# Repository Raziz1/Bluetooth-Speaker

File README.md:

# Bluetooth-Speaker 🛜🔊
 PCB design for a custom bluetooth speaker

<p align="center"><i>KiCad Render</i></p>

## Design Considerations
The goal of this project was to design a simple Bluetooth speaker using parts I already had at home, along with components available in the current KiCad library. This approach aimed to simplify the design process.
Based on the above goal I selected the following components: 

# Components

## ESP32 🖥️
* [ESP32-C3-WROOM-02](https://www.espressif.com/en/module/esp32-c3-wroom-02-en)
* I settled on this ESP32 module because it included the following essential features for this project:
    * Bluetooth 5
    * On-board PCB antenna
    * I2S (Inter-Integrated Circuit Sound)
    * Built-in USB Serial/JTAG Controller
* During my initial research, I planned to use the GPIO DACs to output the audio signal. However, I soon discovered that other models only offered 8-bit DACs, which were insufficient for modern audio quality. As a result, I decided to settle on a chip that supported I2S.
* Lastly, many ESP32 models require a USB to UART chip for programming. I chose this particular model because it has this functionality built in, allowing it to be directly wired to the USB port.

## Lithium Ion Battery 🔋
For the battery, I ended up selecting a pair of lithium-ion batteries I already had at home. The batteries were two 3.7V 2600mAh lithium-ion batteries from PKCELL. The batteries were initially going to be arranged in series in a battery pack to produce an output voltage of 7.4V and a capacity of 2600 mAh. However, after further research, I determined that using a single cell outputting 3.7V would significantly simplify the design. [Li-ion Battery ICR18650 2600mAh 3.7V Datasheet](https://www.parts-express.com/pedocs/specs/142-202--pkcell-flat-top-18650-li-ion-3.7v-2600mah-rechargeable-battery-spec-sheet.pdf). Some important specifications to note about this battery are the following:
* Nominal Voltage - 3.7V
* Charging Cut-off Voltage - 4.2V
* Discharge Cut-off Voltage - 3.0V
* Standard Charge - Constant Current 0.5C Constant Voltage 4.2V 0.01 C cut-off
* Standard Discharge - Discharge at 0.2 C to 3.0V

<p align="center"><i>PKCELL Lithium Ion Batteries</i></p>

## Audio Amplifier 
The audio amplifier was a key factor in determining my lithium-ion battery cell configuration. When selecting an amplifier, I had several requirements:
* It needed to output 2-5 watts with a 4-ohm speaker.
* It had to have built-in support for I2S to simplify the external circuitry.
* It required a low enough supply voltage to be compatible with either a 1S or 2S lithium-ion battery configuration.
Given these requirements, I opted for a Class D amplifier. These amplifiers are the most efficient, requiring the lowest supply voltage, which made them ideal for my battery-powered application.

### Power Considerations
* For Class D audio amplifiers under 5 watts, you can power them with a single 18650 3.7V cell, as they typically operate within a voltage range of 2.5 to 5.5V.
* For Class D audio amplifiers exceeding 5 watts, a higher supply voltage range is necessary, which typically requires a larger series battery configuration. However, when your battery configuration's supply voltage surpasses 5V, standard USB-C charging becomes insufficient. In this case, you have two options:
    1. Use a power delivery IC to negotiate higher voltages (9V, 12V, or 20V) from the wall socket.
    2. Implement a boost converter between the USB-C receptacle and the charger management IC.

I ended up settling on the [MAX98357A](https://www.analog.com/media/en/technical-documentation/data-sheets/MAX98357A-MAX98357B.pdf). Some important specifications to note about this battery are the following:
* Single-Supply Operation (2.5V to 5.5V)
* 3.2W Output Power into 4Ω at 5V
* Supports I2S data

## Charger Management IC
For the charger management IC I ended up settling on the [MAX1811](https://www.analog.com/media/en/technical-documentation/data-sheets/MAX1811.pdf) because of its simplicity and due to the fact it was already in the KiCad library.

# Firmware

# Schematic Design
## USB-C
For the USB-C interface, I opted for a minimal power delivery interface and simply added 5.1k pull-down resistors on both CC lines. Consequently, with a compatible power source (host), this device should be able to draw up to 3A of current.

## MAX1811 (Charging Management IC)
* Battery Regulation Voltage-Select Input was set to high so that the battery regulation set point is 4.20V
* Battery Regulation Current-Selection Input was set to high to default to a 500mA maximum battery regulation current.
    * This charger IC is on the slower side. There exists much higher power charger management IC'selected

## RT6150B-33GQW (Current Mode Buck-Boost Converter)
* The RT6150A/B is a high efficiency, fixed frequency, BuckBoost DC-DC converter that operates from input voltages above, below or equal to the output voltage.

### Inductor Selection
* ${L_1=\frac{V_{out}\cdot \left(V_{in\left(max\right)}-V_{out}\right)}{f\cdot ΔI_L\cdot V_{out}}=\frac{3.3\cdot \:\left(5-3.3\right)}{1E6\cdot 0.15\cdot \:3.3} = 7.48uH}$
* ${L_2=\frac{V_{in\left(min\right)}\cdot \:\left(V_{out}-V_{in\left(min\right)}\right)}{f\cdot \:ΔI_L\cdot \:V_{out}}=\frac{3.1\cdot \:\:\left(3.3-3.1\right)}{1E6\cdot \:0.150\cdot \:\:3.3}=1.25uH}$
* ${ΔI_L}$ The ripple current was chosen to be 30% of the suggested ESP32 power supply output current of at least 500mA.
* The datasheet suggests <i>"The recommended inductor value range is between 1.5μH and 4.7μH."</i>
* Therefore, based on the datasheets suggestions and calculations a reasonable middle ground was to select an inductance of 4.7uH.

### Output Capacitor Selection
* ${ΔV_{out},\:peak\:\left(Buck\right)=100mV=\frac{V_{out}\cdot \:\left(V_{in}-V_{out}\right)}{V_{in}\cdot \:8\cdot \:L\cdot \:\left(f_{osc}\right)^2\cdot \:C_{out}}=\frac{3.3\cdot \:\left(5-3.3\right)}{5\cdot \:8\cdot \:\left(4.7E-6\right)\cdot \:\left(1E6\right)^2\cdot \:C_{out}}\rightarrow C_{out}=2.98E-7F}$
* ${ΔV_{out},\:peak\:\left(Boost\right)=100mV=\frac{I_{Load}\cdot \left(V_{out}-V_{in}\right)}{C_{out}\cdot V_{out}\cdot f_{osc}}=\frac{0.5\:\cdot \:\left(3.3-3.1\right)}{C_{out}\cdot \:3.3\cdot \:\left(1E6\right)}\rightarrow C_{out}=3.03E-7F}$
* The above calculations assume an output ripple voltage of 100mV. Given that said we will use the value that is used on the Raspberry Pi PICO (47uF) which is significantly higher and will result in a significantly smaller output ripple voltage.

### Thermal Considerations
* PD(MAX) = (125°C − 25°C) / (30.5°C/W) = 3.28W for
WDFN-10L 3x3 package

* PD(MAX) = (125°C − 25°C) / (40.9°C/W) = 2.44W for
WDFN-10L 2.5x2.5 package 

# PCB Layout

# BOM

# Characterization

# Resources
* [How to design an ESP32 PCB with KiCad (in less than 25 minutes)
](https://www.youtube.com/watch?v=jiJGbWOSdMo)
* [ESP32 + PCB Antenna Hardware Design Tutorial - Phil's Lab #90
](https://www.youtube.com/watch?v=yxU_Kw2de08)
* [ESP32 PCB Layout Design](https://docs.espressif.com/projects/esp-hardware-design-guidelines/en/latest/esp32c2/pcb-layout-design.html)
* [All About USB-C: Example Circuits
](https://hackaday.com/2023/08/07/all-about-usb-c-example-circuits/)
* [ESP32 Dev Kit Schematic Example](https://dl.espressif.com/dl/schematics/SCH_ESP32-C3-DEVKITC-02_V1_1_20210126A.pdf)
* [I2S MAX98357 Bluetooth Speaker project for ESP32 microcontroller / Programming Arduino IDE](https://www.youtube.com/watch?v=24pk28oqVQI)
* [ESP32 Audio Output with I2S DMA and the MAX98357A Class D Amplifier](https://www.youtube.com/watch?v=At8PDQ3g7FQ)
* [ESP32-A2DP](https://github.com/pschatzmann/ESP32-A2DP)
* [ESP32 DAC Audio Analog Output With Examples (Arduino IDE)](https://deepbluembedded.com/esp32-dac-audio-arduino-examples/)
* [Sound with ESP32 – I2S Protocol](https://dronebotworkshop.com/esp32-i2s/)

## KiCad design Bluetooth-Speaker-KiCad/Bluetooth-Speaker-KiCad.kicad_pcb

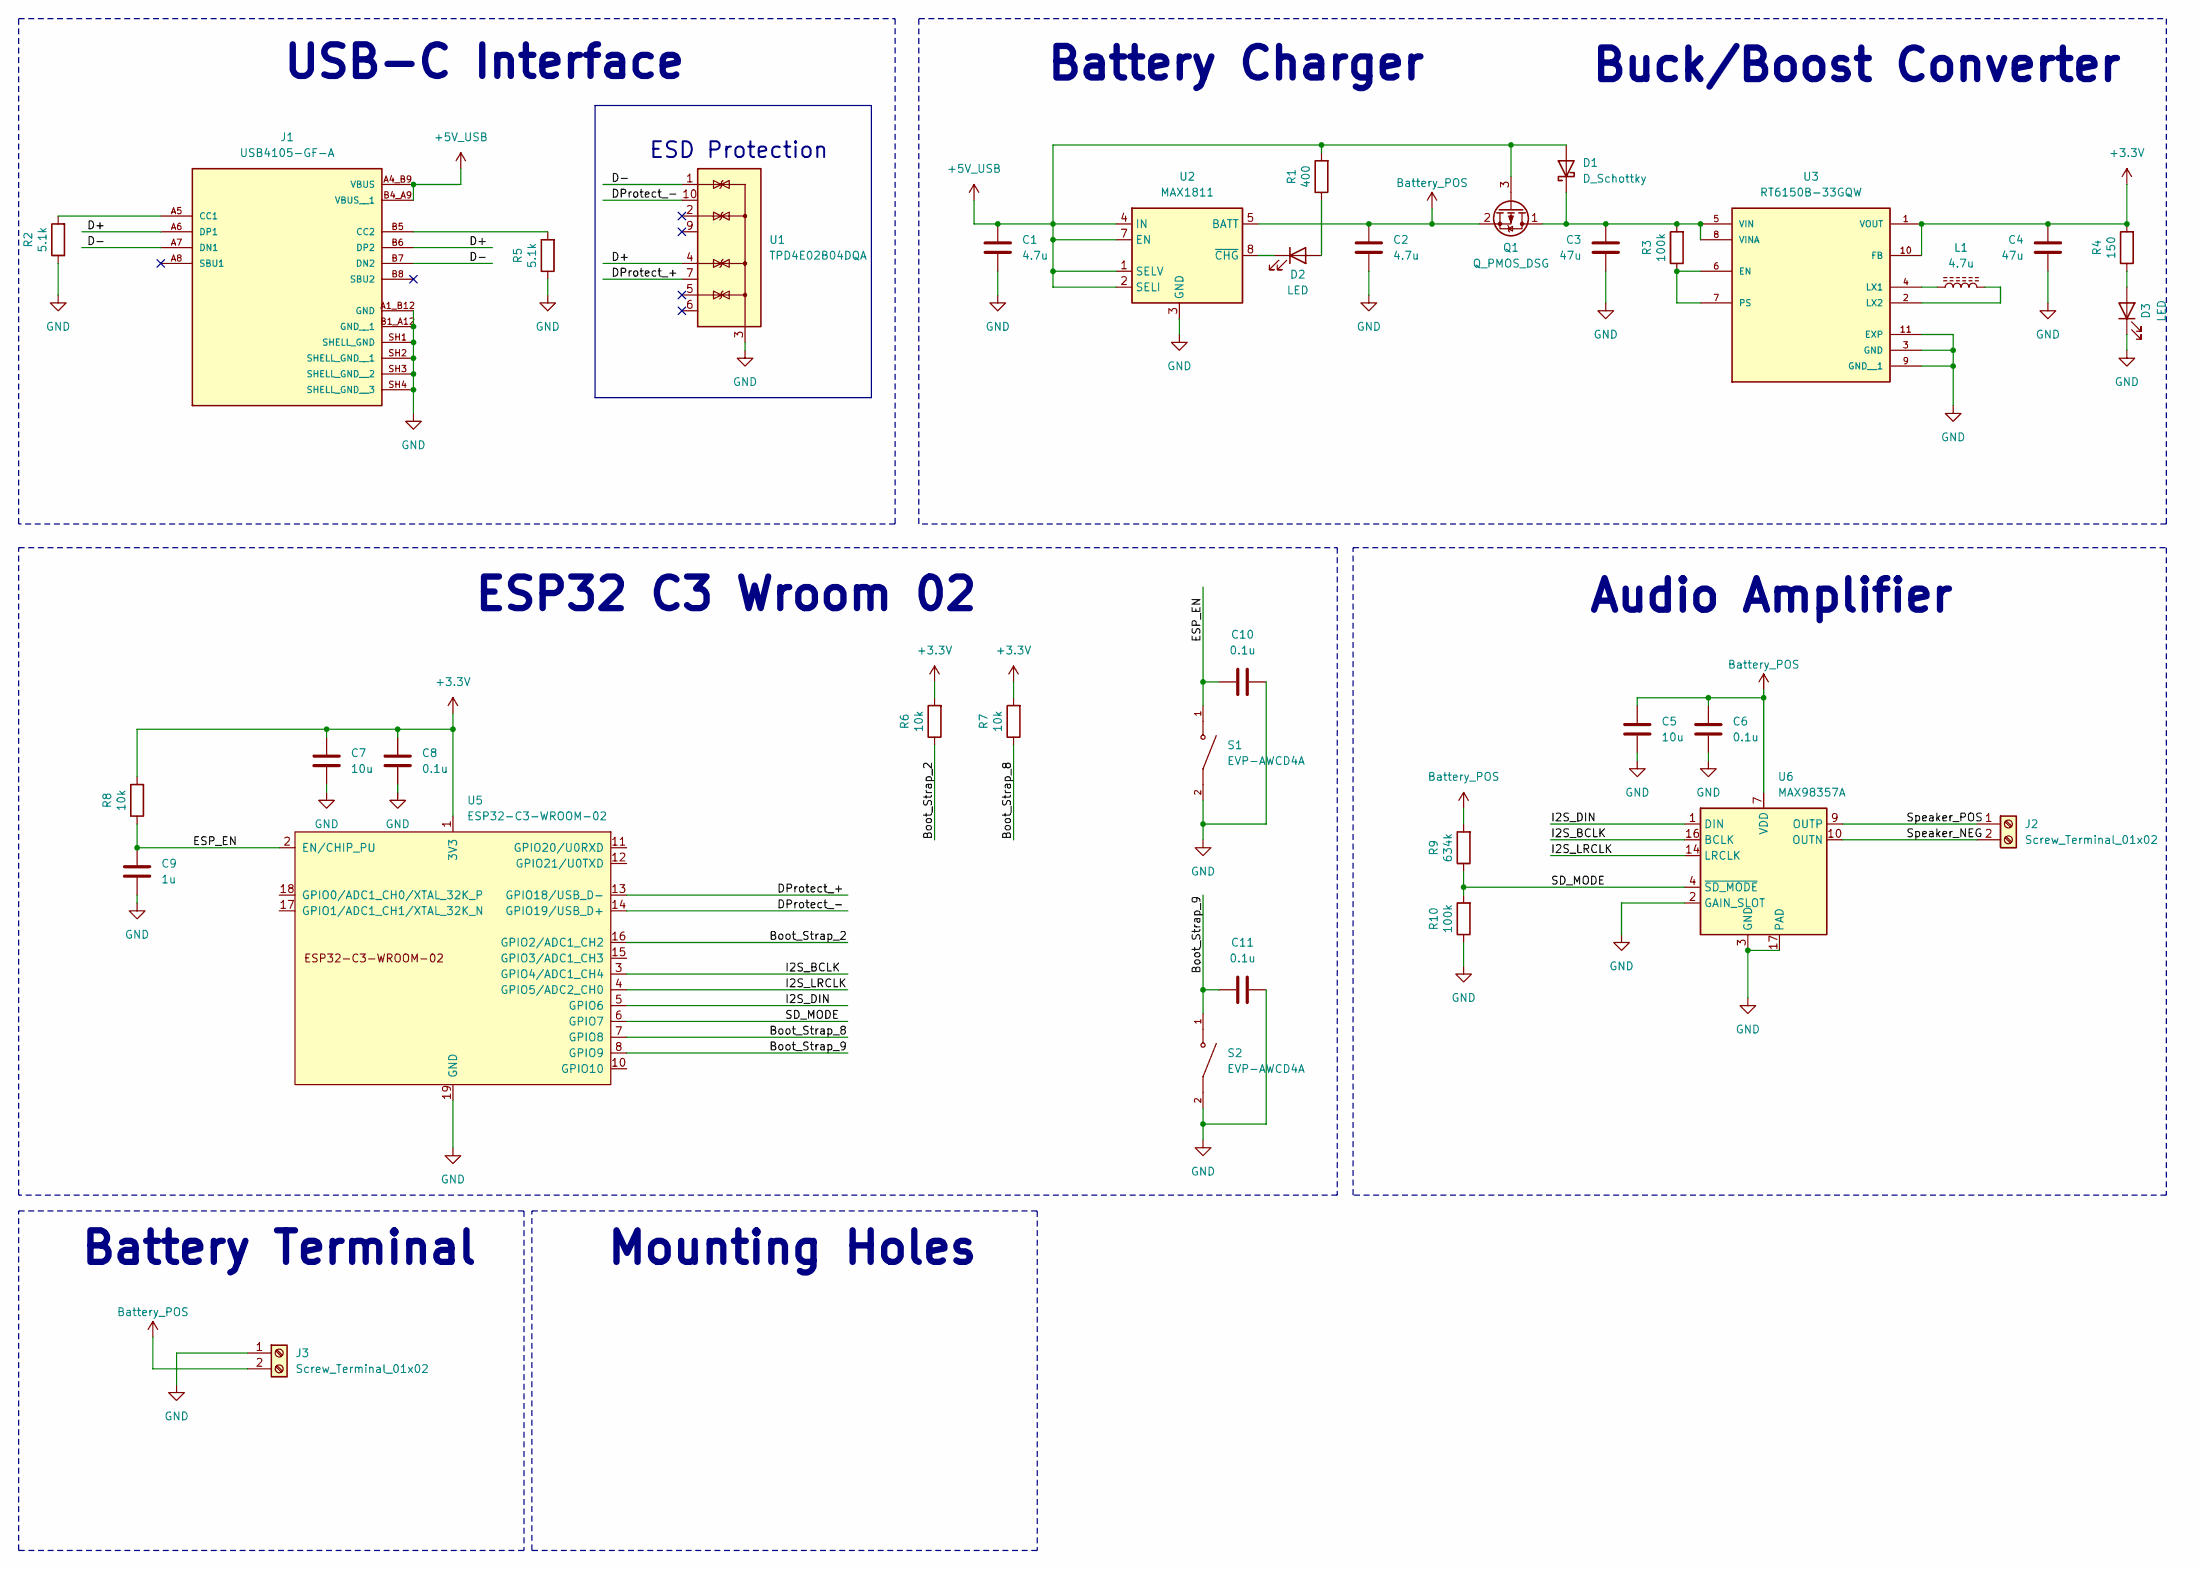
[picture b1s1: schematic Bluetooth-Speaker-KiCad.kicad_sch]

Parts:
C1, C2: 4.7u; C_0603_1608Metric_Pad1.08x0.95mm_HandSolder
C3, C4: 47u; C_0603_1608Metric_Pad1.08x0.95mm_HandSolder
C5, C7: 10u; C_0603_1608Metric_Pad1.08x0.95mm_HandSolder
C6, C8, C10, C11: 0.1u; C_0603_1608Metric_Pad1.08x0.95mm_HandSolder
C9: 1u; C_0603_1608Metric_Pad1.08x0.95mm_HandSolder
D1: D_Schottky; D_0603_1608Metric_Pad1.05x0.95mm_HandSolder
D2, D3: LED; LED_0603_1608Metric_Pad1.05x0.95mm_HandSolder
J1: USB4105-GF-A; GCT_USB4105-GF-A; PARTREV B4
J2, J3: Screw_Terminal_01x02; TerminalBlock_Phoenix_MKDS-1,5-2-5.08_1x02_P5.08mm_Horizont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
L1: 4.7u; L_0805_2012Metric_Pad1.05x1.20mm_HandSolder
Q1: Q_PMOS_DSG; SOT91P240X110-3N_DMG2305UX-7
R1: 400; R_0603_1608Metric_Pad0.98x0.95mm_HandSolder
R2, R5: 5.1k; R_0603_1608Metric_Pad0.98x0.95mm_HandSolder
R3, R10: 100k; R_0603_1608Metric_Pad0.98x0.95mm_HandSolder
R4: 150; R_0603_1608Metric_Pad0.98x0.95mm_HandSolder
R6, R7, R8: 10k; R_0603_1608Metric_Pad0.98x0.95mm_HandSolder
R9: 634k; R_0603_1608Metric_Pad0.98x0.95mm_HandSolder
S1, S2: EVP-AWCD4A; SW_EVP-AWCD4A
U1: TPD4E02B04DQA; USON-10_2.5x1.0mm_P0.5mm
U2: MAX1811; SOIC-8_3.9x4.9mm_P1.27mm
U3: RT6150B-33GQW; SON50P250X250X80-11N; PARTREV July 2018
U5: ESP32-C3-WROOM-02
U6: MAX98357A; TQFN-16-1EP_3x3mm_P0.5mm_EP1.23x1.23mm_ThermalVias

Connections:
+3.3V: C4.1, C7.1, C8.1, R4.2, R6.2, R7.2, R8.2, U3.1 (VOUT), U3.10 (FB), U5.1 (3V3)
+5V_USB: C1.1, D1.2 (A), J1.A4_B9 (VBUS), J1.B4_A9 (VBUS__1), Q1.3 (G), R1.2, U2.1 (SELV), U2.2 (SELI), U2.4 (IN), U2.7 (EN)
/Boot_Strap_2: R6.1, U5.16 (GPIO2/ADC1_CH2)
/Boot_Strap_8: R7.1, U5.7 (GPIO8)
/Boot_Strap_9: C11.1, S2.1, U5.8 (GPIO9)
/D+: J1.A6 (DP1), J1.B6 (DP2), U1.4 (IO3)
/D-: J1.A7 (DN1), J1.B7 (DN2), U1.1 (IO1)
/DProtect_+: U1.7 (NC), U5.13 (GPIO18/USB_D-)
/DProtect_-: U1.10 (NC), U5.14 (GPIO19/USB_D+)
/ESP_EN: C9.1, C10.1, R8.1, S1.1, U5.2 (EN/CHIP_PU)
/I2S_BCLK: U5.3 (GPIO4/ADC1_CH4), U6.16 (BCLK)
/I2S_DIN: U5.5 (GPIO6), U6.1 (DIN)
/I2S_LRCLK: U5.4 (GPIO5/ADC2_CH0), U6.14 (LRCLK)
/SD_MODE: R9.1, R10.2, U5.6 (GPIO7), U6.4 (~SD_MODE)
/Speaker_NEG: J2.2, U6.10 (OUTN)
/Speaker_POS: J2.1, U6.9 (OUTP)
Battery_POS: C2.1, C5.1, C6.1, J3.2, Q1.2 (S), R9.2, U2.5 (BATT), U6.7 (VDD), U6.8 (VDD)
GND: C1.2, C2.2, C3.2, C4.2, C5.2, C6.2, C7.2, C8.2, C9.2, C10.2, C11.2, D3.1 (K), J1.A1_B12 (GND), J1.B1_A12 (GND__1), J1.SH1 (SHELL_GND), J1.SH2 (SHELL_GND__1), J1.SH3 (SHELL_GND__2), J1.SH4 (SHELL_GND__3), J3.1, R2.1, R5.1, R10.1, S1.2, S2.2, U1.3 (G), U1.8 (G), U2.3 (GND), U2.6 (GND), U3.3 (GND), U3.9 (GND__1), U3.11 (EXP), U5.9 (GND), U5.19 (GND), U6.2 (GAIN_SLOT), U6.3 (GND), U6.11 (GND), U6.15 (GND), U6.17 (PAD)
unnamed: C3.1, D1.1 (K), Q1.1 (D), R3.2, U3.5 (VIN), U3.8 (VINA)
unnamed: D2.2 (A), R1.1
unnamed: D2.1 (K), U2.8 (~CHG)
unnamed: D3.2 (A), R4.1
unnamed: J1.A5 (CC1), R2.2
unnamed: J1.B5 (CC2), R5.2
unnamed: R3.1, U3.6 (EN), U3.7 (PS)
unnamed: L1.1, U3.4 (LX1)
unnamed: L1.2, U3.2 (LX2)

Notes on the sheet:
USB-C Interface
ESP32 C3 Wroom 02
Battery Terminal
ESD Protection
Buck/Boost Converter
Mounting Holes
Audio Amplifier
Battery Charger

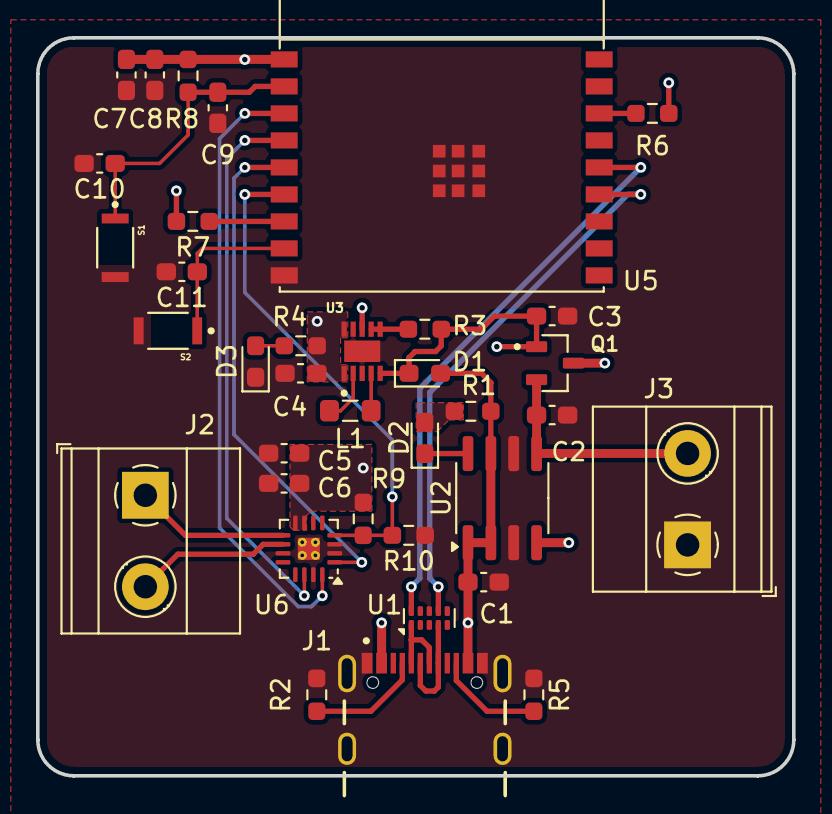
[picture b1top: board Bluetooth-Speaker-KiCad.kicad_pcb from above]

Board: 4 copper layers, 42.0 x 41.0 mm, 36 parts (0 on the bottom side), 27 nets.

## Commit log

2024-12-29 Initial Commits
2024-12-29 USB Connections
2024-12-31 Updated battery charging
2025-01-01 Updated schematics
2025-01-03 Updated schematic
2025-01-05 Updated README File
2025-01-05 Updated layout
2025-01-05 Added Images
2025-01-05 Updated Resources Section
2025-01-06 Removed mounting holes
2025-01-08 Updated layout with switches
2025-01-08 Updated final PCB render
